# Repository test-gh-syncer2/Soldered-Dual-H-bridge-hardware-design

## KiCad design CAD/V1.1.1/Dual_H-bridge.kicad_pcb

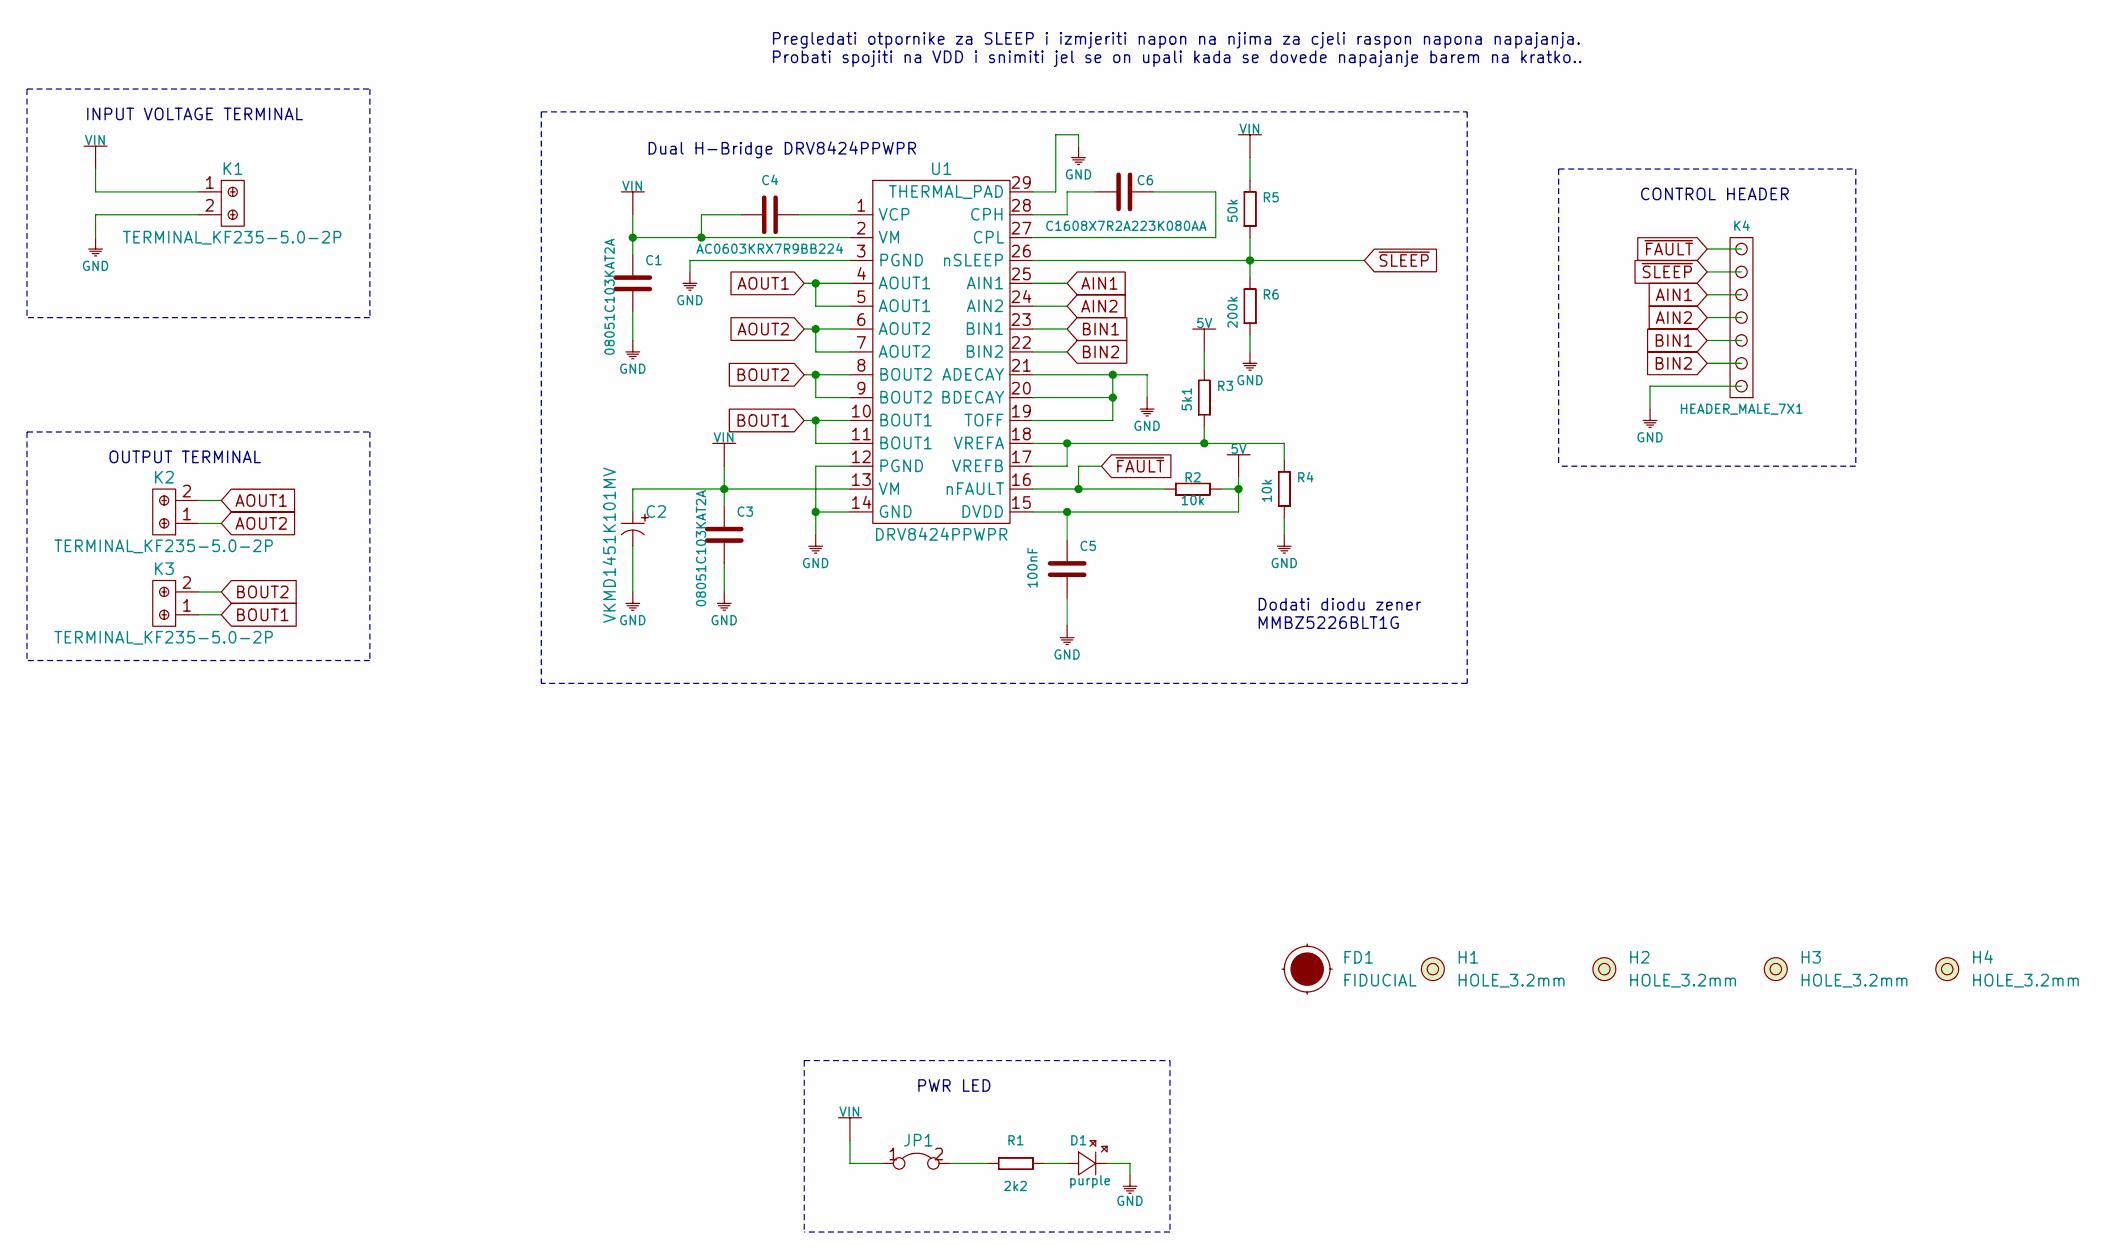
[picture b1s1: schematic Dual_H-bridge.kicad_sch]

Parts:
C1, C3: 08051C103KAT2A; 0805C
C2: VKMD1451K101MV; ELECTROLITIC_CAP_8x8x14.5
C4: AC0603KRX7R9BB224; 0603C
C5: 100nF; 0603C
C6: C1608X7R2A223K080AA; 0603C
D1: purple; 0402LED
FD1: FIDUCIAL; FIDUCIAL_23
H1, H2, H3, H4: HOLE_3.2mm
JP1: SMD-JUMPER-CONNECTED_TRACE_SLODERMASK
K1, K2, K3: TERMINAL_KF235-5.0-2P
K4: HEADER_MALE_7X1
R1: 2k2; 0402R
R2, R4: 10k; 0603R
R3: 5k1; 0603R
R5: 50k; 0603R
R6: 200k; 0603R
U1: DRV8424PPWPR; HTSSOP-28

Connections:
5V: C5.2, R2.2, R3.2, U1.15 (DVDD)
AIN1: K4.5, U1.25 (AIN1)
AIN2: K4.4, U1.24 (AIN2)
AOUT1: K2.2, U1.4 (AOUT1), U1.5 (AOUT1)
AOUT2: K2.1, U1.6 (AOUT2), U1.7 (AOUT2)
BIN1: K4.3, U1.23 (BIN1)
BIN2: K4.2, U1.22 (BIN2)
BOUT1: K3.1, U1.10 (BOUT1), U1.11 (BOUT1)
BOUT2: K3.2, U1.8 (BOUT2), U1.9 (BOUT2)
GND: C1.1, C2.2 (-), C3.1, C5.1, D1.2 (K), K1.2, K4.1, R4.1, R6.1, U1.3 (PGND), U1.12 (PGND), U1.14 (GND), U1.19 (TOFF), U1.20 (BDECAY), U1.21 (ADECAY), U1.29 (THERMAL_PAD)
unnamed: C4.2, U1.1 (VCP)
unnamed: C6.1, U1.27 (CPL)
unnamed: C6.2, U1.28 (CPH)
unnamed: D1.1 (A), R1.2
unnamed: JP1.2, R1.1
unnamed: R3.1, R4.2, U1.17 (VREFB), U1.18 (VREFA)
VIN: C1.2, C2.1 (+), C3.2, C4.1, JP1.1, K1.1, R5.2, U1.2 (VM), U1.13 (VM)
~FAULT: K4.7, R2.1, U1.16 (nFAULT)
~SLEEP: K4.6, R5.1, R6.2, U1.26 (nSLEEP)

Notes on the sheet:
INPUT VOLTAGE TERMINAL
OUTPUT TERMINAL
Pregledati otpornike za SLEEP i izmjeriti napon na njima za cjeli raspon napona napajanja. Probati spojiti na VDD i snimiti jel se on upali kada se dovede napajanje barem na kratko..
Dual H-Bridge DRV8424PPWPR
PWR LED
Dodati diodu zener MMBZ5226BLT1G
CONTROL HEADER

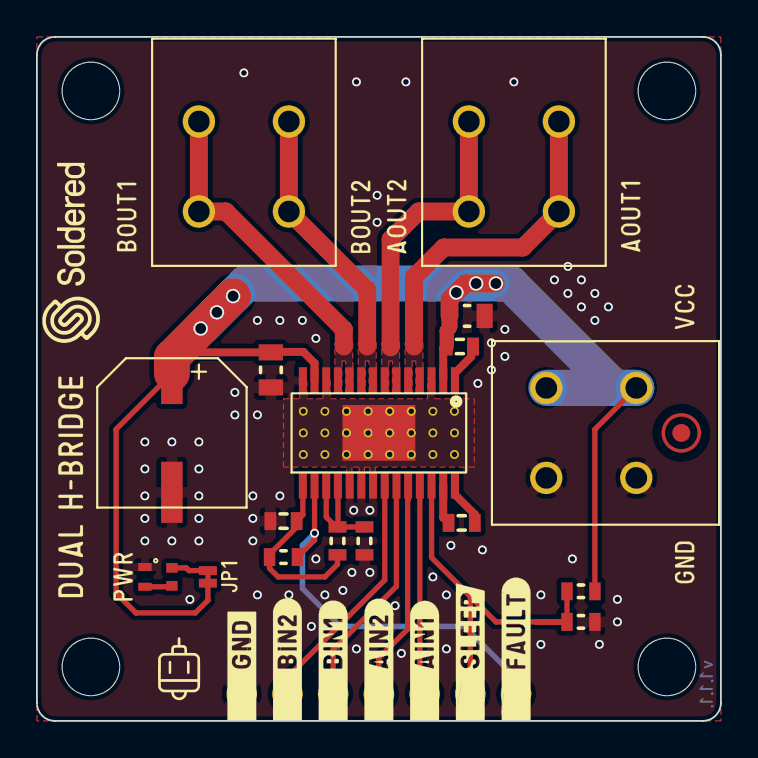
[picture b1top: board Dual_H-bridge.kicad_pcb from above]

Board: 2 copper layers, 38.0 x 38.0 mm, 24 parts (0 on the bottom side), 19 nets.

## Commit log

2021-09-23 Syncing to git
2021-09-23 Updating open source files.
